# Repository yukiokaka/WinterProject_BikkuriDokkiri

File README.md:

WinterProject_BikkuriDokkiri
============================

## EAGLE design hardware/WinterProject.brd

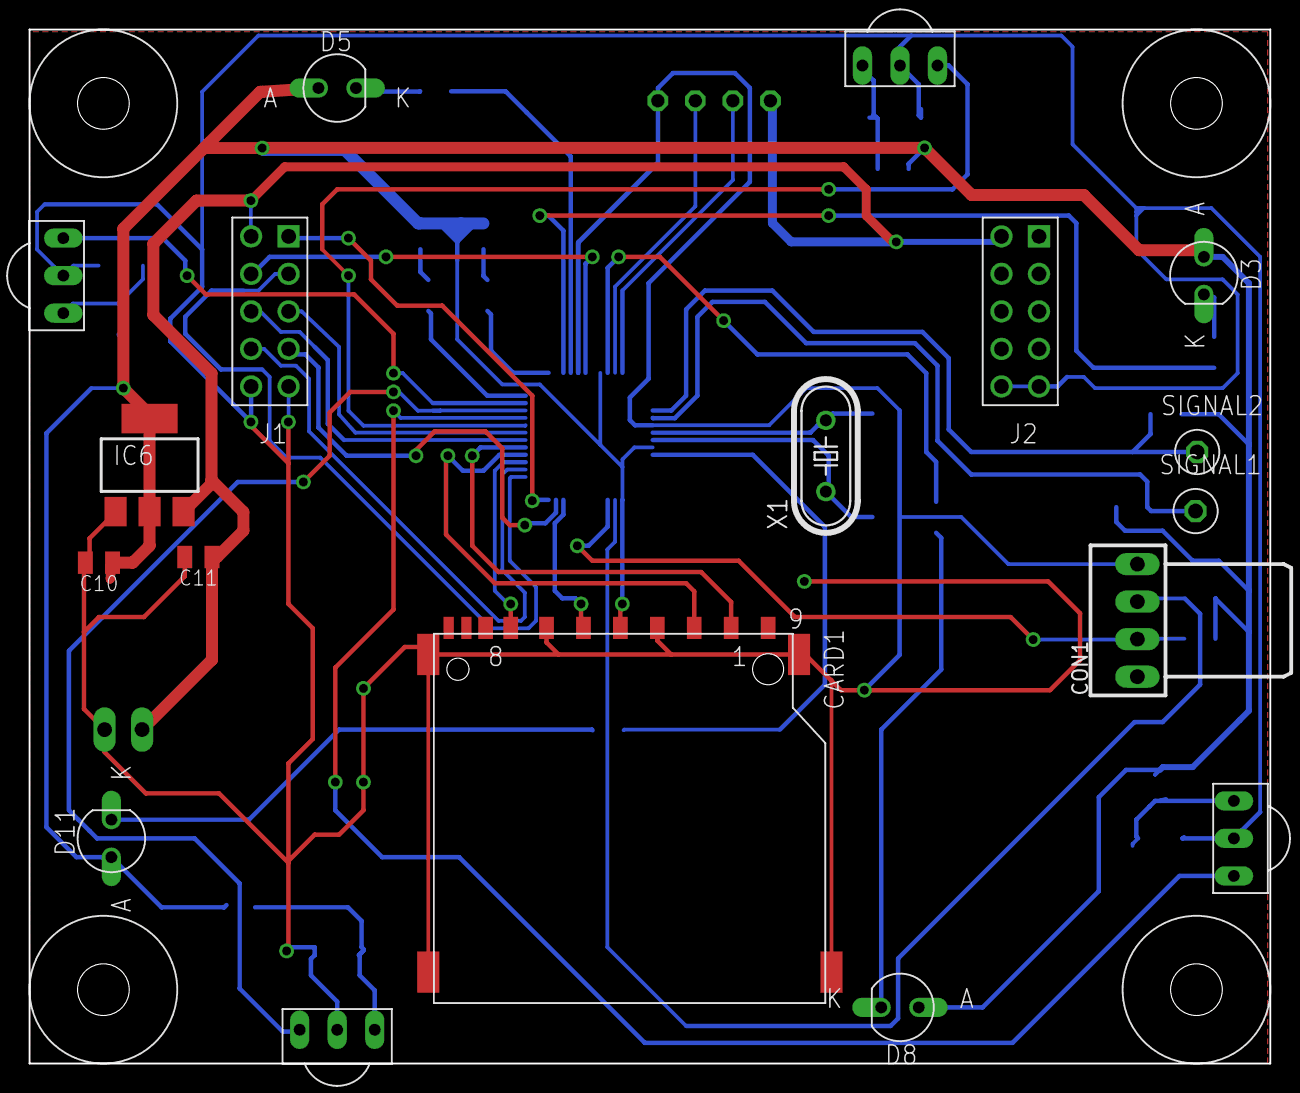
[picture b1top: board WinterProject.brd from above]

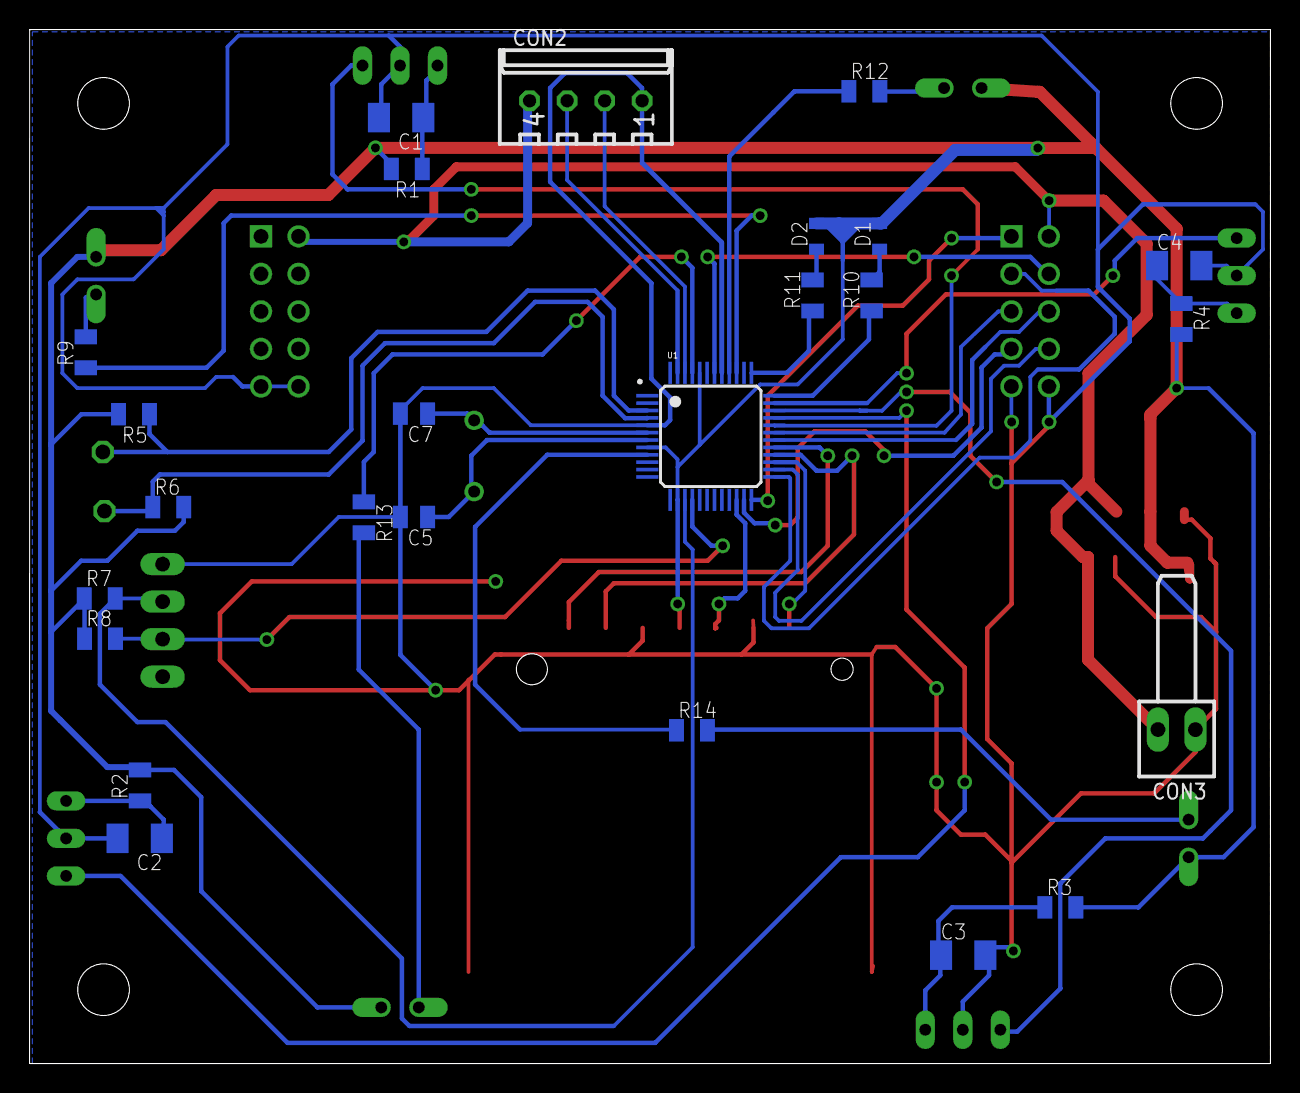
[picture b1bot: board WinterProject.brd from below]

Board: 2 copper layers, 84.0 x 70.0 mm, 42 parts (25 on the bottom side), 42 nets.

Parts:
C1, C2, C3, C4: 4u710V; 3216@1
C5, C7: 100n; 2012-C
C10: 22uF; 2012-C
C11: 10uF; 2012-C
CARD1: SD-AKI-C00753; C-1734234
CON1: I2C-A; 5251-04-A
CON2: UART-S; IL-G-04-S
CON3: RT-2PIN-A; 5251-02-A
D1, D2: LED-SMD1608; D1608
D3, D5, D8, D11: TLN105B; LED5_OFFSET
IC1, IC2, IC3, IC4: PL-IRM0101-3; PL-IRM0101
IC6: AZ1086H-3.3; SOT223
R1, R2, R3, R4, R10, R11: 100; 2012-R
R5, R6, R7, R8, R9, R12, R13, R14: 1k; 2012-R
SIGNAL1, SIGNAL2: CHECK_PIN; SLC-22-G
U1: LQFP48
U$1: 16X16DOTMATRIX_MODULE
X1: HC49/S

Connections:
+5V: C11.1, CON2.4, CON3.2, IC6.IN, U$1.J1VCC, U$1.J2VCC
GND: C1.2, C2.2, C3.2, C4.2, C5.2, C7.2, C10.2, C11.2, CARD1.3, CARD1.6, CARD1.GND1, CARD1.GND2, CARD1.GND3, CARD1.GND4, CON1.4, CON2.1, CON3.1, IC1.GND, IC2.GND, IC3.GND, IC4.GND, IC6.GND, U1.5, U1.41, U$1.J1GND, U$1.J1OIE, U$1.J2GND, U$1.J2OIE
IR0: IC1.VOUT, U1.32
IR1: IC2.VOUT, U1.33
IR2: IC3.VOUT, U1.34
IR3: IC4.VOUT, U1.35
IRLED0: R9.1, U1.39
IRLED1: R12.1, U1.40
IRLED2: R13.1, U1.45
IRLED3: R14.1, U1.9
J1OIA: U1.24, U$1.J1OIA
J1OIB: U1.25, U$1.J1OIB
J1OIC: U1.31, U$1.J1OIC
J1OID: U1.23, U$1.J1OID
J1RCK: U1.42, U$1.J1RCK
J1SCK: U1.30, U$1.J1SCK
J1SER: U1.26, U$1.J1SER
unnamed: C2.1, IC2.VCC, R2.1
unnamed: C3.1, IC3.VCC, R3.1
unnamed: C1.1, IC1.VCC, R1.1
unnamed: C4.1, IC4.VCC, R4.1
unnamed: C7.1, U1.6, X1.2
unnamed: CON1.2, R8.2, U1.16
unnamed: CON2.3, U1.47
unnamed: CON2.2, U1.46
unnamed: R5.1, SIGNAL2.SIGNAL, U1.3
unnamed: R6.1, SIGNAL1.SIGNAL, U1.4
unnamed: CON1.3, R7.2, U1.15
unnamed: D3.K, R9.2
unnamed: D5.K, R12.2
unnamed: D8.K, R13.2
unnamed: D11.K, R14.2
unnamed: D1.K, R10.2
unnamed: D2.K, R11.2
unnamed: R10.1, U1.36
unnamed: R11.1, U1.37
unnamed: C5.1, U1.7, X1.1
SD_CLK: CARD1.5, U1.22
SD_CS: CARD1.1, U1.29
SD_DIN: CARD1.2, U1.28
SD_DOUT: CARD1.7, U1.27
VCC: C10.1, CARD1.4, D1.A, D2.A, D3.A, D5.A, D8.A, D11.A, IC6.OUT, IC6.VOUT, R1.2, R2.2, R3.2, R4.2, R5.2, R6.2, R7.1, R8.1, U1.8, U1.14, U1.44

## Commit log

2013-12-22 added circuit data
2013-12-22 modified structure of directories
2013-12-23 modified schematic, but gpio is too few, so it maybe change main microcontroller LPC1114 into STM32 or LPC11C24
2013-12-24 modified sch and brd
2013-12-25 modified brd
2013-12-30 rewired WinterProject.sch for using 16x16 DotMatrixLED
2013-12-30 added library for 16x16 module
2013-12-30 modified board data to rearrange the place of via hole and wire, but the number of via is too many, so it should redraw some wires
2013-12-30 rebased master
2013-12-30 modified brd
    reduced vias
2014-01-03 modified +5V and Vcc lines
2014-01-03 confirmed DRC
2014-01-03 modified library expand hole
2014-01-04 modified 16x16 matrix LED lbr bug
2014-01-10 added MARY Board Program
2014-01-10 deleted unnecessary files
2014-01-10 deleted obj file
2014-01-10 deleted i2c source
2014-01-10 deleted obj
2014-01-10 deleted test code
2014-01-10 adde write command into Makefile
2014-01-10 changed base program
2014-01-10 added spi command code
2014-01-10 added code for reading fatfs
2014-01-10 added gitignore
2014-01-11 modified code
2014-01-11 deleted
2014-01-11 commit mmcbb.c
2014-01-11 restore
2014-01-11 del files
2014-01-11 added SD format tool
2014-01-11 deleted unnecessary comment
2014-01-12 added supply connector and changed regulator IC
2014-01-13 added ircomm program
2014-01-13 successed ir communication prototype
2014-01-13 added checksum mechanism
2014-01-13 add display.c
    made the functions that initiates the matrix LED, and displays a 16x16
    data dynamically on it. (I haven’t tested on the circuit yet.)
2014-01-14 added header file for display.c
2014-01-14 refactoring ircomm.c
2014-01-14 Revert "refactoring ircomm.c"
    This reverts commit df9185af44e17aae0d44de44231924b0aff85042.
2014-01-14 add define _BV in display.c
2014-01-14 added arrays for displaying dot-pictures of "1", "2", "3", "4"
2014-01-15 for display
2014-01-15 modified display.c for shrinking array size
2014-01-15 added a dot picture of '0'
2014-01-16 modified brd and sch (opened J2 pins and connected J1OID to PIO0_7)
2014-01-16 added ircomm test communication
2014-01-16 added code for ping
2014-01-16 added pc-microcontroller uart communication
2014-01-16 modified display_module program
2014-01-16 added openCV and UART communication for PC side
2014-01-16 added code for transmitting display data
2014-01-16 modifeid code for merge
2014-01-16 deleted unnecessary timer control
2014-01-18 modified ircomm
2014-01-18 modified ircomm_recv for dynamic change of ir senssor
2014-01-18 added device num data in send/recv protocol
2014-01-18 added functino pointor array
2014-01-18 added next_ping system
2014-01-20 modified pccom decrease latency time
2014-01-21 added NVOL flash program
2014-01-22 arrange indent
